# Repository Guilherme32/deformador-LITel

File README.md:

# Deformador do LITel

Esse repositório guarda o que foi desenvolvido de parte eletrônica / de código
do deformador do LITel.

# Informações

O deformador é um equipamento construído para aplicar uma deformação controlada
a uma placa de teste. A placa é afixada em uma extremidade, enquanto que a
outra é conectada a um cabo de aço que pode fazer uma força para baixo,
deformando o material com uma flecha. Um dinamômetro entre a placa e o cabo de
aço mede a força constantemente, para que o sistema possa ser usado para
calibração de sensores. O cabo de aço é puxado por um sistema com um motor de
passo e um fuso, controlado por um esp8266 através de duas interfaces
possíveis.

Embora o sistema tenha a possibilidade de visualização do movimento do fuso do
motor, é recomendado que se use apenas a força lida no dinamômetro para
calibração de sensores. Isso se dá porque a distância percorrida no fuso não
é igual à distância da flecha na placa, por conta dos componentes que estão no
meio do caminho.

# Interface Física

A interface mais simples de se usar é a física, composta de 7 botões. Com o
lado dos botões para cima, e o conector à esquerda, a função dos botões são,
seguindo da esquerda para a direita:

- Botão 1: Recua 5cm (alivia a carga);
- Botão 2: Recua 5mm (alivia a carga);
- Botão 3: Recua 1mm (alivia a carga);
- Botão 4: Interrompe o movimento;
- Botão 5: Avança 1mm (aumenta a carga);
- Botão 6: Avança 5mm (aumenta a carga);
- Botão 7: Avança 5cm (aumenta a carga);

Caso os botões sejam segurados, os comandos serão continuamente repetidos,
sendo que os valores são atualizados a partir do atual. Dessa forma, o sistema
irá iniciar o movimento ao pressionar o botão, e irá se mover pelo valor do
botão após ser soltado.

> Por exemplo, se o botão 3 for segurado por 2 segundos, e então solto, o
> sistema irá recuar continuamente por 2 segundos, e após isso ainda irá recuar
> mais 1mm.

Os botões mais extremos movem a flecha por valores consideravelmente grandes, e
foram feitos com o objetivo de colocar um alvo distante e de que os comandos
sejam interrompidos manualmente.

Com essa interface, não há como saber a distância percorrida no fuso do motor.

# Interface Web

Para o uso da interface web, é necessário o uso de um dispositivo que esteja
conectado à mesma rede local do esp8266 e seja capaz de renderizar páginas web
(HTML, CSS e JS). O esp possui a função de ponto de acesso, permitindo a
que o dispositivo se conecte diretamente a ele, caso possua conectividade WiFi.

## Ponto de Acesso (Access Point)

As credenciais de acesso do modo de ponto de acesso são as seguintes:

> SSID: deformador-litel
> Senha: 787Cu7kg

Nesse modo, o programa pode ser acessado através do ip:

> ip: 192.168.4.1

## Modo Estação (Station)

O esp também pode se conectar a uma rede externa. Isso aumenta a confiabilidade
do sistema, porque o ponto de acesso do esp não é muito estável. Para que ele
se conecte, é necessário que primeiro o dispositivo acesse o programa pelo
ponto de acesso, e então configure as credenciais da rede externa pela página
de conexão. Na página de conexão é possível ver o status (se conseguiu
conectar) e o endereço de ip.

Com o dispositivo conectado à mesma rede externa, o endereço ip do esp deverá
ser utilizado para acessar a aplicação.

> O esp tentará se conectar à última rede configurada sempre que for ligado.

## Páginas

### Página Principal

A página principal serve apenas como entrada à interface. Ela permite acesso às
outras páginas do sistema, e também tem o link do repositório no GitHub.

> Todas as páginas possuem os mesmos links presentes nessa.

### Conexão

Essa página mostra as informações de conexão (SSID, senha, ip), e permite mudar
as credenciais da rede a ser acessada pelo modo estação. Também indica se o
modo de estação está conectado devidamente.

### Controle

Essa página é a que permite a interface principal do sistema. Através daqui é
possível visualizar a posição atual do motor, o deslocamento correspondente no
fuso, e também enviar novos comandos para o sistema.

Os componentes importantes da página são:

- Comandos: É possível enviar dois comandos para o sistema:
  - Deslocar: Envia uma nova posição alvo para o deslocamento. Esse comando não
              é cumulativo, o valor enviado é o alvo, não um valor a mover;
  - Encontrar zero: Envia o comando de reset de zero. O sistema entrará na
                    sequência de detecção, não podendo receber outros comandos
                    e recuando (aliviando a carga) até que encontrar o sensor
                    de fim de curso;
- Informações: Algumas informações são dispostas no centro da página:
  - Progresso: Uma barra cresce da esquerda para a direita, indicando o
               progresso do último comando;
  - Estado: O estado do sistema, que pode ser "movendo", "parado" ou
            "procurando zero"
  - Posição: A posição e correspondente deslocamento atuais no fuso do motor.

> !! O DESLOCAMENTO NÃO DEVE SER USADO PARA CALIBRAÇÃO !! É possível calcular a
> deformação da placa a partir da flecha, mas não é trivial calcular a flecha
> a partir do deslocamento do fuso. Os deslocamentos não serão iguais, porque
> o cabo de aço, o dinamômetro e outros componentes no meio do caminho se
> deformam

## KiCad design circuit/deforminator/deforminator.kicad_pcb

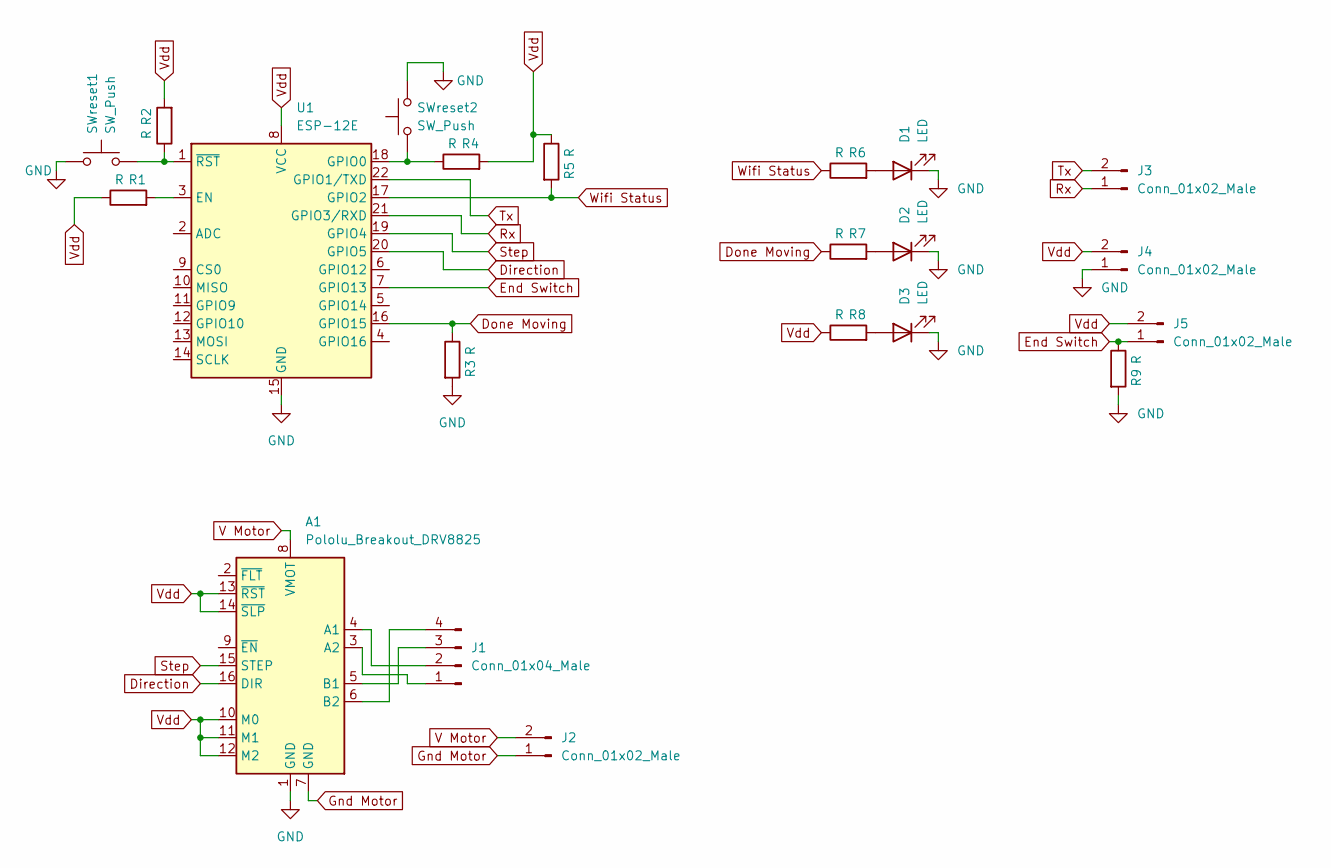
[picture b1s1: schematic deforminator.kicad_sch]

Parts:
A1: Pololu_Breakout_DRV8825; Pololu_Breakout-16_15.2x20.3mm
D1, D2, D3: LED; LED_D3.0mm_Clear
J1: Conn_01x04_Male; PinHeader_1x04_P2.54mm_Vertical
J2, J3, J4, J5: Conn_01x02_Male; PinHeader_1x02_P2.54mm_Vertical
R1, R2, R3, R4, R5, R6, R7, R8, R9: R; R_Axial_DIN0207_L6.3mm_D2.5mm_P7.62mm_Horizontal
SWreset1, SWreset2: SW_Push; SW_PUSH_6mm
U1: ESP-12E

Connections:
Direction: A1.16 (DIR), U1.20 (GPIO5)
Done Moving: R3.1, R7.1, U1.16 (GPIO15)
End Switch: J5.1, R9.1, U1.7 (GPIO13)
GND: A1.1 (GND), D1.1 (K), D2.1 (K), D3.1 (K), J4.1, R3.2, R9.2, SWreset1.1, SWreset2.2, U1.15 (GND)
Gnd Motor: A1.7 (GND), J2.1
unnamed: A1.3 (A2), J1.1
unnamed: A1.4 (A1), J1.2
unnamed: A1.5 (B1), J1.3
unnamed: A1.6 (B2), J1.4
unnamed: D3.2 (A), R8.2
unnamed: R1.2, U1.3 (EN)
unnamed: R2.1, SWreset1.2, U1.1 (~RST)
unnamed: R4.1, SWreset2.1, U1.18 (GPIO0)
unnamed: D1.2 (A), R6.2
unnamed: D2.2 (A), R7.2
Rx: J3.1, U1.21 (GPIO3/RXD)
Step: A1.15 (STEP), U1.19 (GPIO4)
Tx: J3.2, U1.22 (GPIO1/TXD)
V Motor: A1.8 (VMOT), J2.2
Vdd: A1.10 (M0), A1.11 (M1), A1.12 (M2), A1.13 (~RST), A1.14 (~SLP), J4.2, J5.2, R1.1, R2.2, R4.2, R5.1, R8.1, U1.8 (VCC)
Wifi Status: R5.2, R6.1, U1.17 (GPIO2)

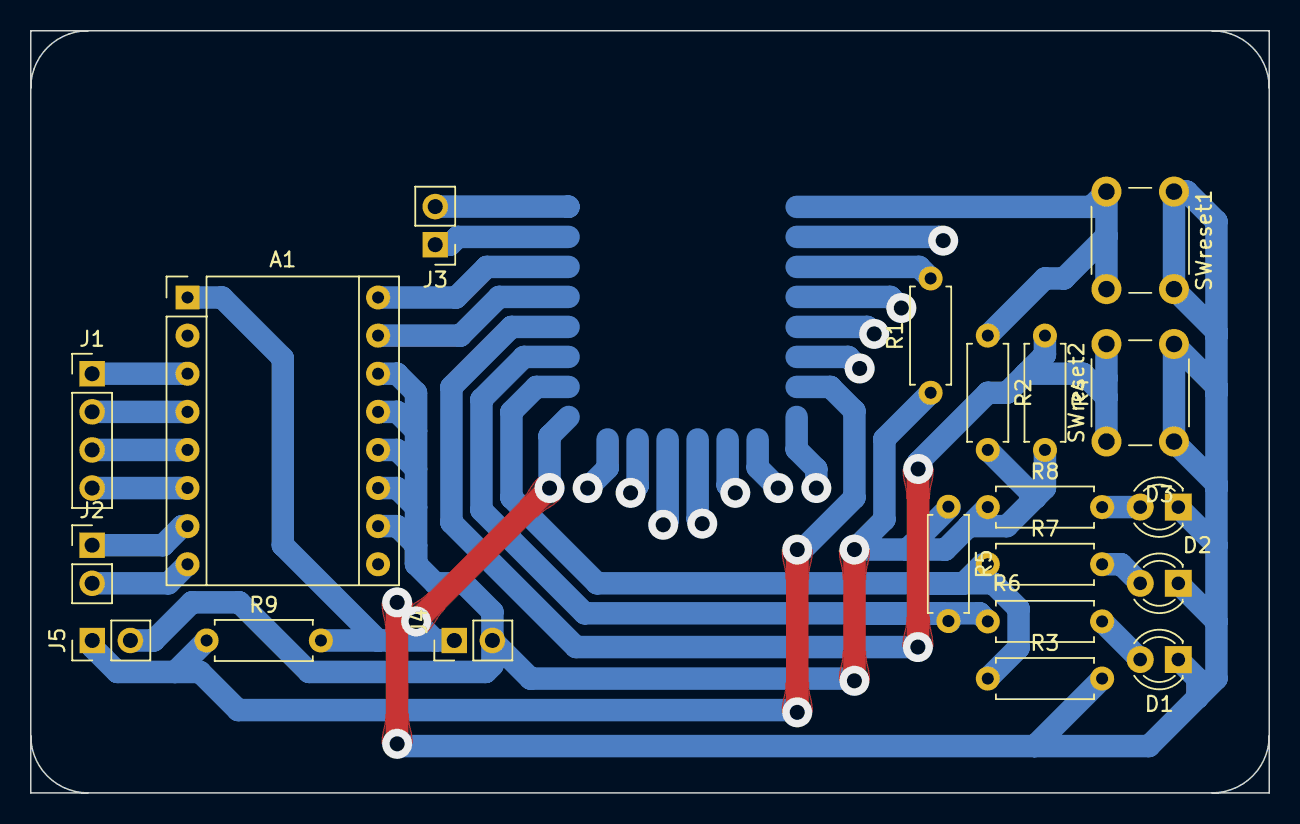
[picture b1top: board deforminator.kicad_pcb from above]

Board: 2 copper layers, 82.6 x 50.8 mm, 21 parts (1 on the bottom side), 21 nets.

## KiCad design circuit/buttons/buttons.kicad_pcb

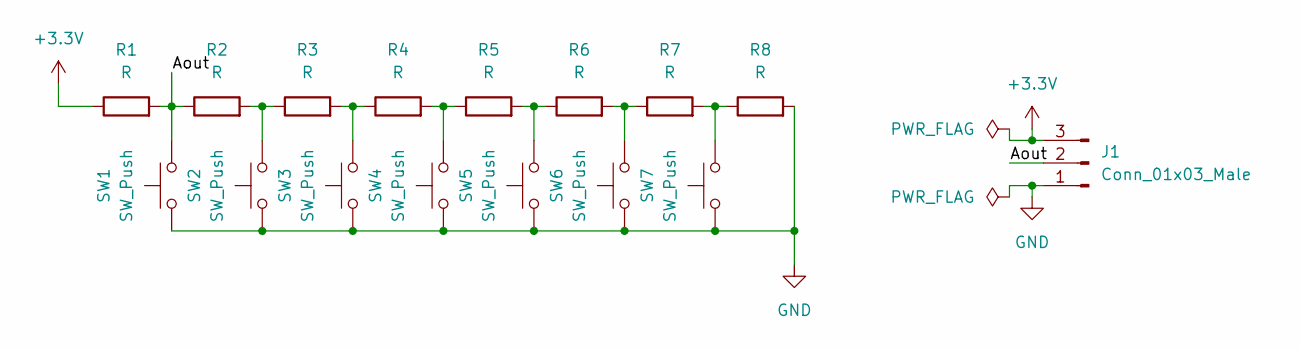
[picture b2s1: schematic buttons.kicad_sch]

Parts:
J1: Conn_01x03_Male; PinHeader_1x03_P2.54mm_Vertical
R1, R2, R3, R4, R5, R6, R7, R8: R; R_Axial_DIN0207_L6.3mm_D2.5mm_P7.62mm_Horizontal
SW1, SW2, SW3, SW4, SW5, SW6, SW7: SW_Push; SW_PUSH-12mm

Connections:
+3V3: J1.3, R1.1
/Aout: J1.2, R1.2, R2.1, SW1.2
GND: J1.1, R8.2, SW1.1, SW2.1, SW3.1, SW4.1, SW5.1, SW6.1, SW7.1
unnamed: R2.2, R3.1, SW2.2
unnamed: R3.2, R4.1, SW3.2
unnamed: R4.2, R5.1, SW4.2
unnamed: R5.2, R6.1, SW5.2
unnamed: R6.2, R7.1, SW6.2
unnamed: R7.2, R8.1, SW7.2

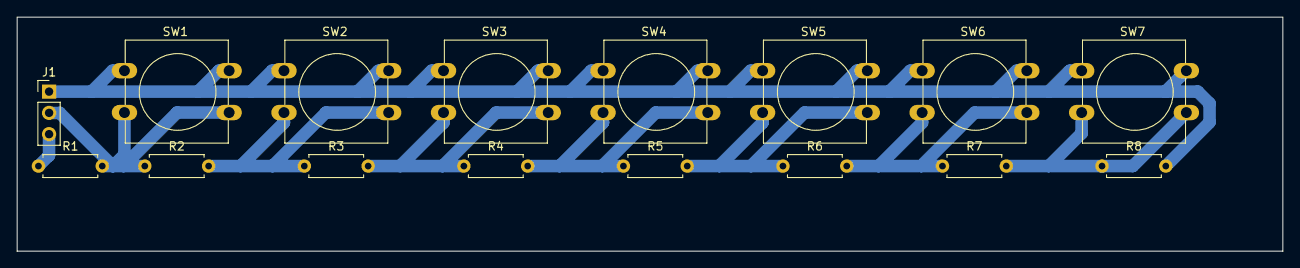
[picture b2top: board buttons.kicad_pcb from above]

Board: 2 copper layers, 151.1 x 27.9 mm, 16 parts (0 on the bottom side), 9 nets.

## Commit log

2023-06-29 Documenting firmware
2023-06-30 Add readme
2023-06-30 Documenting
